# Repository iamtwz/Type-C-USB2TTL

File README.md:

一个使用 CH340C 的 USB Type-C 转串口模块

## 功能

- 具有 DTR 引脚，并且可选择是否串联 0.1uF 电容，可实现 Arduino 自动下载
- VCC 电压 5V 与 3V3 可选
- 使用 CH340C，无需外部晶振
- 使用 0805 封装，方便焊接

更多内容：「[做点好玩的：使用 Type-C 的 USB 转串口](https://www.jimmytian.com/archives/a-usb-c-to-ttl-module.html)」

----------

A USB Type-C to TTL Serial Module with CH340C

## Features

- A DTR pin and a optionally 0.1uF capacitor in series, can automatic download Arduino programs.
- VCC 5V and 3V3 selectable
- Using CH340C and no external crystal is required
- Using 0805 package and can be easily soldered

To read more(in Chinese): 「[做点好玩的：使用 Type-C 的 USB 转串口](https://www.jimmytian.com/archives/a-usb-c-to-ttl-module.html)」

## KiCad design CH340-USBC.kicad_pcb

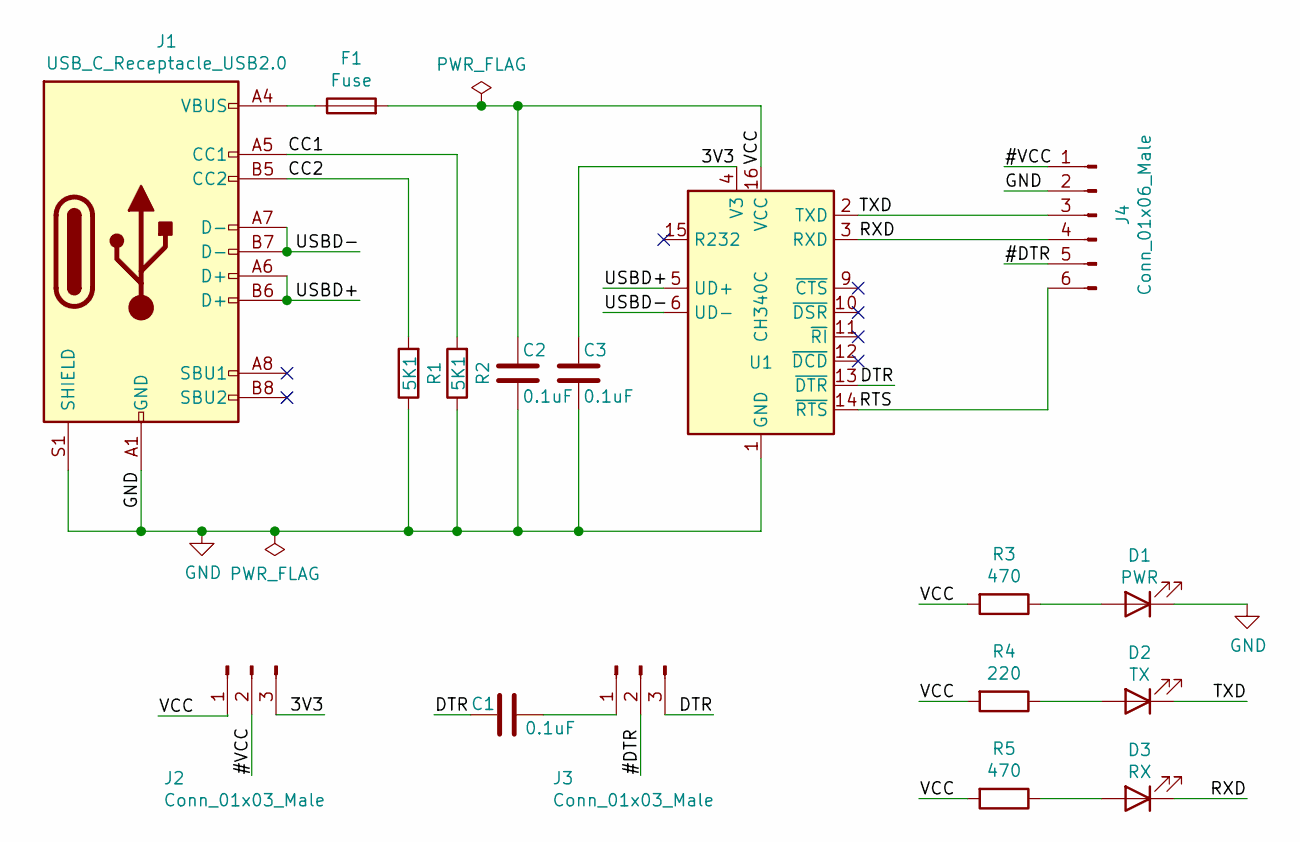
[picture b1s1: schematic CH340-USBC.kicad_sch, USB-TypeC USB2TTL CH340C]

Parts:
C1, C2, C3: 0.1uF; C_0805_2012Metric
D1: PWR; LED_0805_2012Metric
D2: TX; LED_0805_2012Metric
D3: RX; LED_0805_2012Metric
F1: Fuse; Fuse_0805_2012Metric
J1: USB_C_Receptacle_USB2.0; USB_C_Receptacle_HRO_TYPE-C-31-M-12
J2, J3: Conn_01x03_Male; PinHeader_1x03_P2.54mm_Vertical
J4: Conn_01x06_Male; PinHeader_1x06_P2.54mm_Horizontal
R1, R2: 5K1; R_0805_2012Metric
R3, R5: 470; R_0805_2012Metric
R4: 220; R_0805_2012Metric
U1: CH340C; SOIC-16_3.9x9.9mm_P1.27mm

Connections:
/3V3: C3.1, J2.3, U1.4 (V3)
/#DTR: J3.2, J4.5
/#VCC: J2.2, J4.1
/CC1: J1.A5 (CC1), R2.2
/CC2: J1.B5 (CC2), R1.2
/DTR: C1.1, J3.3, U1.13 (~DTR)
/RTS: J4.6, U1.14 (~RTS)
/RXD: D3.1 (K), J4.4, U1.3 (RXD)
/TXD: D2.1 (K), J4.3, U1.2 (TXD)
/USBD+: J1.A6 (D+), J1.B6 (D+), U1.5 (UD+)
/USBD-: J1.A7 (D-), J1.B7 (D-), U1.6 (UD-)
/VCC: C2.1, F1.2, J2.1, R3.2, R4.2, R5.2, U1.16 (VCC)
GND: C2.2, C3.2, D1.1 (K), J1.A1 (GND), J1.A12 (GND), J1.B1 (GND), J1.B12 (GND), J1.S1 (SHIELD), J4.2, R1.1, R2.1, U1.1 (GND)
unnamed: C1.2, J3.1
unnamed: D1.2 (A), R3.1
unnamed: D2.2 (A), R4.1
unnamed: D3.2 (A), R5.1
unnamed: F1.1, J1.A4 (VBUS), J1.A9 (VBUS), J1.B4 (VBUS), J1.B9 (VBUS)
no_connect_19: J1.A8 (SBU1)
no_connect_20: J1.B8 (SBU2)
no_connect_21: U1.10 (~DSR)
no_connect_22: U1.11 (~RI)
no_connect_23: U1.12 (~DCD)
no_connect_24: U1.15 (R232)
no_connect_25: U1.7 (NC)
no_connect_26: U1.8 (NC)
no_connect_27: U1.9 (~CTS)

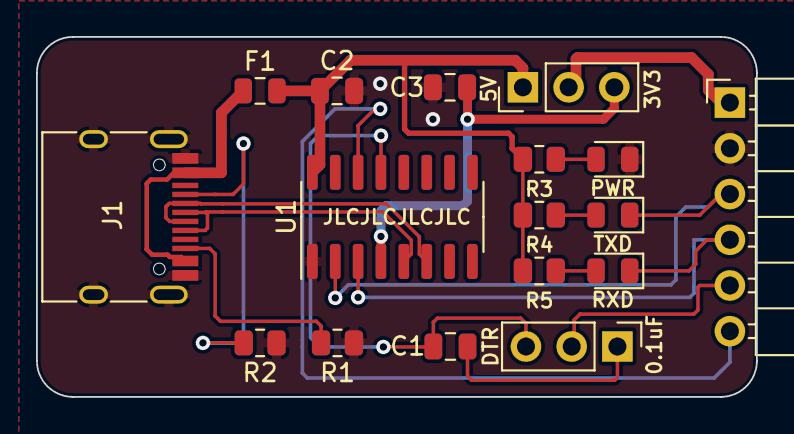
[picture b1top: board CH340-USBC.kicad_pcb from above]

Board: 2 copper layers, 40.0 x 20.0 mm, 17 parts (0 on the bottom side), 18 nets.

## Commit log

2020-12-26 V1.1 Release
